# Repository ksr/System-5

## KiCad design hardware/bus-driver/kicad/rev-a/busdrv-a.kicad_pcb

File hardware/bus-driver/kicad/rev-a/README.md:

# System-5 Bus Driver Rev A (BUSDRV-A): KiCad master

> **AS ORDERED 2026-10-09 (JLCPCB 2000765A-Y53): SCRAP. Kept as the record of what was made; do not order from it.**
> This board file has four copper layers (inherited from memory Rev D's Eagle import), and Freerouting put 234 of its 247 track segments on In1/In2. The 2-layer zip held only the top and bottom copper, so the made boards have only GND (the pours), -INT, SDA, Q and one +5V segment; `tools/check_order_zip.py` fails this zip. Found 2026-10-19.
> **The replacement is Rev B (BUSDRV-B), `../rev-b/`:** the same circuit re-routed as a true 2-layer board, with 0.1" bypass caps.

A System-5 card modelled on the YACC1 bus tester. An **Arduino Nano** on USB drives two **MCP23017** I²C expanders wired straight onto the 30-pin System-5 bus.
- With the **CPU card removed**, it is bus master: it can read and write memory and I/O cards by running the 1802's bus cycle itself.
- With the **CPU in**, it only monitors.

Designed 2026-10-06. Generated by `gen/` from one netlist (`gen/netlist.py`). Edit `gen/netlist.py` and re-run the scripts, or edit in KiCad and drop the generator.

## Circuit

| Part | What it does |
|---|---|
| A1 Arduino Nano | USB serial console. I²C on A4 (SDA) and A5 (SCL). D2/D3 take the expanders' INTA. D4 drives XRST (both expanders' reset). A0 reads BUS_SENSE. |
| U1 MCP23017 @ 0x20 | GPA0–6 = D0–D6, GPB0–6 = A0–A6, GPA7/GPB7 = SPARE1/SPARE2 |
| U2 MCP23017 @ 0x21 | GPA0–6 = D7, A7, TPA, TPB, -MRD, -MRW, -VMA. GPB0–6 = Q, -RESET, -INT, -EF, N0, N1, N2. GPA7/GPB7 = SPARE3/SPARE4. |
| J1 | System-5 30-pin bus. Same footprint and position as on every System-5 card. |
| J2 | SPARE1–4 (outputs only), +5V, GND, for flying leads or later the CPU card's mode lines |
| R1, R2 4.7k | I²C pull-ups, to bus +5V |
| R3 10k | XRST pull-up, to bus +5V |
| R4 10k / R5 100k | Bus +5V sense into A0 (reads about 4.5 V when the bus is up) |
| R6 470 / D1 | Bus power LED |
| C1, C2 0.1 µF / C3 10 µF | Bypass and bulk |

**Design points:**
- **Output-only pins:** MCP23017 **GPA7/GPB7 are output-only** on current silicon (Microchip datasheet). So all 28 bus signals sit on bidirectional pins, which can be read when monitoring. The four output-only pins are the spares.
- **Power:**
  - The Nano runs from its USB port; its +5V pin is *not* connected to the bus.
  - The expanders and pull-ups run from bus +5V.
  - So USB never feeds a powered-down System-5.

  The firmware should keep D4 low and SDA/SCL released while BUS_SENSE shows the bus is off. Otherwise the Nano's pins back-feed the unpowered expanders through their protection diodes.
- **Bus lines:**
  - The bus lines are connected directly, without series resistors (Ken's choice, as on YACC1).
  - Open-collector lines (-RESET, -INT, -EF) must only ever be driven low or left floating (firmware).
  - The firmware must not drive the bus with the CPU card plugged in: the 1802 drives its address lines even in reset.
- **At power-up and on XRST:** the MCP23017 pins are inputs, so the card is quiet on the bus until the firmware decides otherwise.

## Board

- **Size and layout:** 140.95 × 96.19 mm, 2 layers. The System-5 card outline and bus connector position are taken from the Memory Rev D board.
  - The Nano sits on the right, with its USB socket at the card's outer edge.
  - The power LED is in the standard System-5 position.
- **Routing:** Freerouting; 247 track segments, 7 vias. Signals 0.25 mm, +5V/GND 0.6 mm, GND pour on both sides. JLCPCB 2-layer rules.
- **Checks, 2026-10-06:**
  - ERC: 0.
  - Netlist proof: MATCH, 41/41 nets.
  - DRC: 0 violations, 0 unconnected.
  - Schematic parity: 0.
- **Silkscreen:** chip labels with function and I²C address; "R1 4.7k"-style values; spare-header pin names; title `BUSDRV-A`.

**Check before ordering:** the Nano on female headers stands about 15–20 mm tall. Make sure that fits the card pitch in the System-5 cage, and that a USB cable can reach the card's outer edge with the card installed.

## Files

| File | What it is |
|---|---|
| `busdrv-a.kicad_pro/.kicad_sch/.kicad_pcb` | The project |
| `busdrv.pretty/C30.kicad_mod` | System-5 bus connector footprint (from the Eagle C30 package) |
| `busdrv-a-gerbers.zip` (and `gerbers/`) | **Upload to JLCPCB**: 2 layers, 1.6 mm |
| `busdrv-a-bom.csv` | Parts list (stock KiCad footprints; all through-hole) |
| `busdrv-a-schematic.pdf`, `-placement.pdf`, `-render-top.png`, `-render-bottom.png` | Prints and pictures |
| `reports/` | Netlist, DRC, ERC |
| `gen/netlist.py`, `make_schematic.py`, `make_board.py` | The generator: netlist → schematic → board |

To regenerate:

```bash
python3 gen/make_schematic.py
```
```bash
kicad-cli sch export netlist --format kicadsexpr -o reports/netlist.net busdrv-a.kicad_sch
```
```bash
<KiCad python> gen/make_board.py
```

Then route as in `tools/kicad/kicad_route.py`.

## Firmware and host tool

- **Firmware:** `embedded/bus-driver/s5-bus-driver`. It compiles for the Nano with arduino-cli. It never ran on a Rev A board (scrap); it has run on BUSDRV-B since 2026-10-30 (`../rev-b/README.md`).
- **Host tool:** `software/busdrv/s5busdrv.py`, with a simulator and tests.
- **Machine cycle:** both run the 1802 cycle: high address byte on A0–7 with a TPA pulse, low byte, -VMA low, then -MRD (read D0–D7) or data on D0–D7 with a -MRW pulse.

Open items for this card are in `BACKLOG.md`.

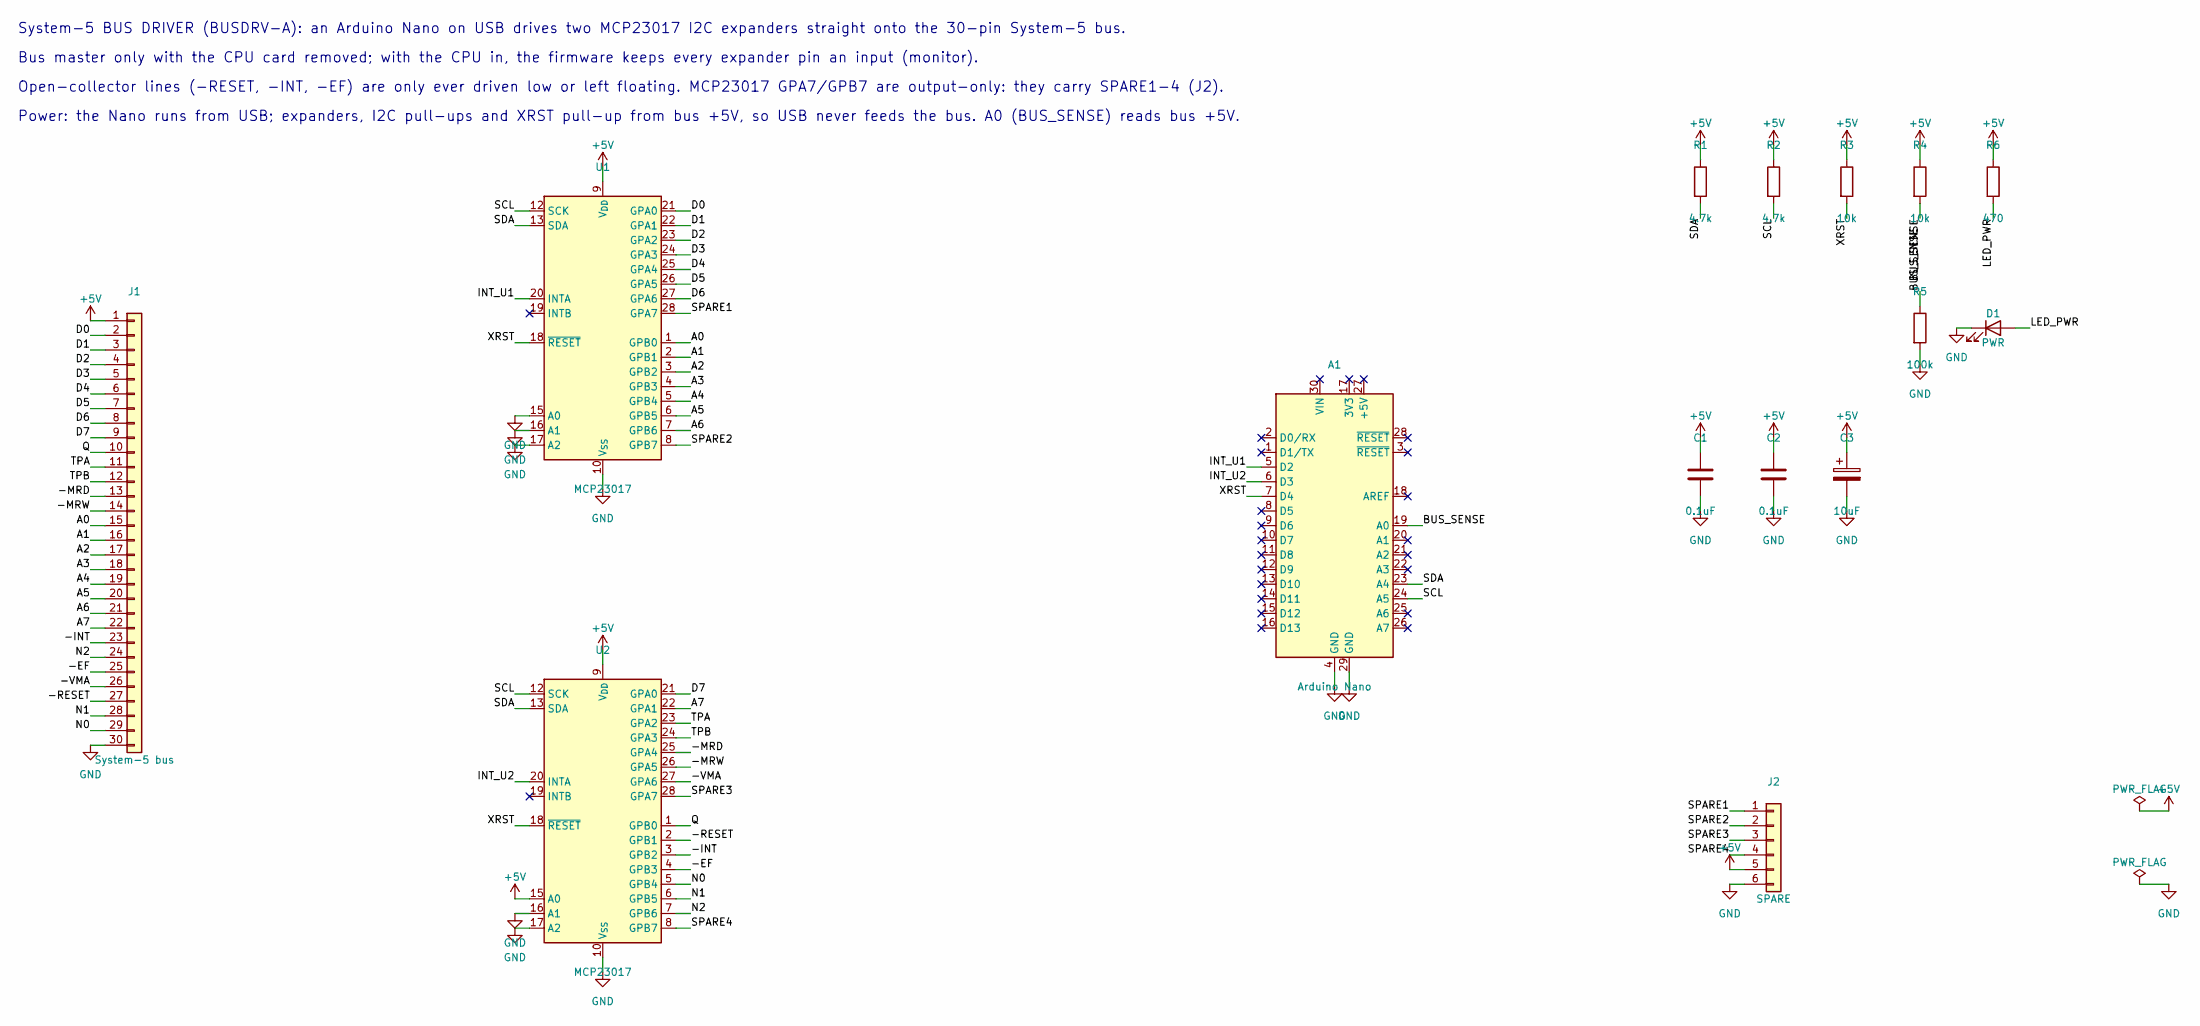
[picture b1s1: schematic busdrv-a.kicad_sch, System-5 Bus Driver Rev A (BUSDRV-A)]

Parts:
A1: Arduino Nano; Arduino_Nano
C1, C2: 0.1uF; C_Disc_D5.0mm_W2.5mm_P5.00mm
C3: 10uF; CP_Radial_D5.0mm_P2.00mm
D1: PWR; LED_D5.0mm
J1: System-5 bus; C30
J2: SPARE; PinHeader_1x06_P2.54mm_Vertical
R1, R2: 4.7k; R_Axial_DIN0207_L6.3mm_D2.5mm_P7.62mm_Horizontal
R3, R4: 10k; R_Axial_DIN0207_L6.3mm_D2.5mm_P7.62mm_Horizontal
R5: 100k; R_Axial_DIN0207_L6.3mm_D2.5mm_P7.62mm_Horizontal
R6: 470; R_Axial_DIN0207_L6.3mm_D2.5mm_P7.62mm_Horizontal
U1, U2: MCP23017; DIP-28_W7.62mm

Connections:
+5V: C1.1, C2.1, C3.1, J1.1, J2.5, R1.1, R2.1, R3.1, R4.1, R6.1, U1.9 (V_{DD}), U2.9 (V_{DD}), U2.15 (A0)
/-EF: J1.25, U2.4 (GPB3)
/-INT: J1.23, U2.3 (GPB2)
/-MRD: J1.13, U2.25 (GPA4)
/-MRW: J1.14, U2.26 (GPA5)
/-RESET: J1.27, U2.2 (GPB1)
/-VMA: J1.26, U2.27 (GPA6)
/A0: J1.15, U1.1 (GPB0)
/A1: J1.16, U1.2 (GPB1)
/A2: J1.17, U1.3 (GPB2)
/A3: J1.18, U1.4 (GPB3)
/A4: J1.19, U1.5 (GPB4)
/A5: J1.20, U1.6 (GPB5)
/A6: J1.21, U1.7 (GPB6)
/A7: J1.22, U2.22 (GPA1)
/BUS_SENSE: A1.19 (A0), R4.2, R5.1
/D0: J1.2, U1.21 (GPA0)
/D1: J1.3, U1.22 (GPA1)
/D2: J1.4, U1.23 (GPA2)
/D3: J1.5, U1.24 (GPA3)
/D4: J1.6, U1.25 (GPA4)
/D5: J1.7, U1.26 (GPA5)
/D6: J1.8, U1.27 (GPA6)
/D7: J1.9, U2.21 (GPA0)
/INT_U1: A1.5 (D2), U1.20 (INTA)
/INT_U2: A1.6 (D3), U2.20 (INTA)
/LED_PWR: D1.2 (A), R6.2
/N0: J1.29, U2.5 (GPB4)
/N1: J1.28, U2.6 (GPB5)
/N2: J1.24, U2.7 (GPB6)
/Q: J1.10, U2.1 (GPB0)
/SCL: A1.24 (A5), R2.2, U1.12 (SCK), U2.12 (SCK)
/SDA: A1.23 (A4), R1.2, U1.13 (SDA), U2.13 (SDA)
/SPARE1: J2.1, U1.28 (GPA7)
/SPARE2: J2.2, U1.8 (GPB7)
/SPARE3: J2.3, U2.28 (GPA7)
/SPARE4: J2.4, U2.8 (GPB7)
/TPA: J1.11, U2.23 (GPA2)
/TPB: J1.12, U2.24 (GPA3)
/XRST: A1.7 (D4), R3.2, U1.18 (~RESET), U2.18 (~RESET)
GND: A1.4 (GND), A1.29 (GND), C1.2, C2.2, C3.2, D1.1 (K), J1.30, J2.6, R5.2, U1.10 (V_{SS}), U1.15 (A0), U1.16 (A1), U1.17 (A2), U2.10 (V_{SS}), U2.16 (A1), U2.17 (A2)

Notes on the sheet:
System-5 BUS DRIVER (BUSDRV-A): an Arduino Nano on USB drives two MCP23017 I2C expanders straight onto the 30-pin System-5 bus.
Bus master only with the CPU card removed; with the CPU in, the firmware keeps every expander pin an input (monitor).
Open-collector lines (-RESET, -INT, -EF) are only ever driven low or left floating. MCP23017 GPA7/GPB7 are output-only: they carry SPARE1-4 (J2).
Power: the Nano runs from USB; expanders, I2C pull-ups and XRST pull-up from bus +5V, so USB never feeds the bus. A0 (BUS_SENSE) reads bus +5V.

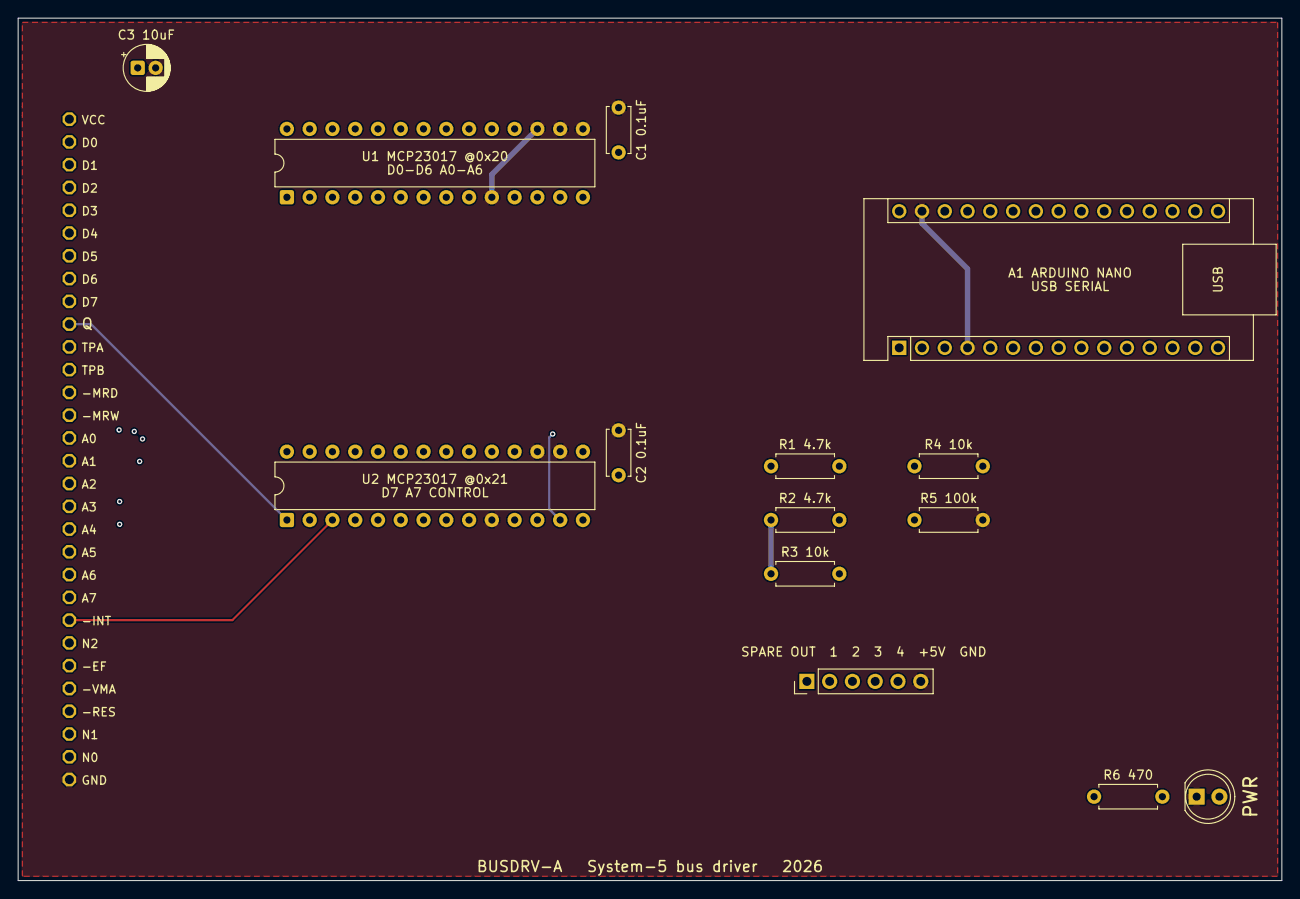
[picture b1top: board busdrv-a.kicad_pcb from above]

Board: 4 copper layers, 140.9 x 96.2 mm, 15 parts (0 on the bottom side), 41 nets.

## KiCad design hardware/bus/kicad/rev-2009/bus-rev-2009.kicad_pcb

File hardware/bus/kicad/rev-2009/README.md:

# bus-rev-2009 — KiCad conversion

Generated 2026-10-26 by `tools/eagle_to_kicad_all.py` from the Fusion XML export of the Eagle design `bus` in `hardware/bus/eagle/rev-2009/fusion-export/`. **The Eagle files are the record of what was designed and built; this KiCad project is derived from them and is regenerated from scratch on every run of the tool** (hand edits here will be lost - once a card is edited in KiCad, remove it from the tool's list). This revision was never fabricated (or its build status is unknown, see `hardware/FABRICATED.md`).

## Files

| File | What it is |
|---|---|
| `bus-rev-2009.kicad_pro` | project; DRC uses OSH Park rules (6 mil track, 5 mil clearance, 10 mil drill, 4 mil annular) as a modern-fab check, not the 2005 fab's rules |
| `bus-rev-2009.kicad_sch` | root sheet; 1 sub-sheet(s) `bus-rev-2009-sheetN.kicad_sch` mirror the Eagle sheets |
| `bus-rev-2009-eagle.kicad_sym` | project symbol library generated from the Eagle libraries used (units = Eagle gates) |
| `bus-rev-2009.kicad_pcb` | the board: 4 copper layers, 15 footprints, 200 track segments, 0 vias; 2 items on unmapped Eagle layers dropped |
| `bus-rev-2009-eagle.pretty/` | project footprint library extracted from the imported board |
| `reports/` | ERC (`erc.json`), DRC (`drc.json`), schematic PDF, board renders (`-top.png`, `-bottom.png`), netlist + `netlist-compare.txt` |

## Proof

Schematic-vs-board netlist comparison (`tools/kicad/compare_netlists.py`: every (reference, pad) partition must be identical): **MATCH (36/36 nets)**

```
  same connectivity, different net name: [('/Sheet 1/5V', '5V'), ('/Sheet 1/A0', 'A0'), ('/Sheet 1/A1', 'A1'), ('/Sheet 1/A2', 'A2'), ('/Sheet 1/A3', 'A3'), ('/Sheet 1/A4', 'A4'), ('/Sheet 1/A5', 'A5'), ('/Sheet 1/A6', 'A6'), ('/Sheet 1/A7', 'A7'), ('/Sheet 1/D0', 'D0'), ('/Sheet 1/D1', 'D1'), ('/Sheet 1/D2', 'D2'), ('/Sheet 1/D3', 'D3'), ('/Sheet 1/D4', 'D4'), ('/Sheet 1/D5', 'D5'), ('/Sheet 1/D6', 'D6'), ('/Sheet 1/D7', 'D7'), ('/Sheet 1/EF', 'EF'), ('/Sheet 1/EF1', 'EF1'), ('/Sheet 1/EF2', 'EF2'), ('/Sheet 1/EF3', 'EF3'), ('/Sheet 1/EXP', 'EXP'), ('/Sheet 1/INP', 'INP'), ('/Sheet 1/INT', 'INT'), ('/Sheet 1/MRD', 'MRD'), ('/Sheet 1/MRW', 'MRW'), ('/Sheet 1/N0', 'N0'), ('/Sheet 1/N1', 'N1'), ('/Sheet 1/N2', 'N2'), ('/Sheet 1/OUT', 'OUT'), ('/Sheet 1/Q', 'Q'), ('/Sheet 1/RESET', 'RESET'), ('/Sheet 1/TPA', 'TPA'), ('/Sheet 1/TPB', 'TPB'), ('/Sheet 1/VMA', 'VMA')]
```

## Readability

`tools/kicad/sch_overlaps.py` over every sheet: text over text 0, text over a symbol body 6, text crossed by a line 0, items off the drawing frame or on the title block 0. What is left is mostly the Eagle drawing itself (parts placed that close in Eagle) or KiCad drawing pin numbers centred on short pins.

## Residual ERC / DRC

ERC by type: power_pin_not_driven 2, unconnected_wire_endpoint 60.
`isolated_pin_label` = the converter's per-net global labels (cosmetic); `power_pin_not_driven` / unused-unit notes are the same ones KiCad's own Eagle importer leaves. `unconnected_wire_endpoint` / `pin_not_connected` = wire stubs Eagle leaves bare (mostly net wires ending on a bus, which is drawn as graphics here); since 2026-09-23 the converter no longer hangs a label on every such end (that was most of the label clutter), so they show as KiCad warnings.

DRC by type: shorting_items 1, silk_over_copper 7, solder_mask_bridge 1, track_dangling 3; unconnected items 0; schematic parity 0.
Silk-over-pad and clearance notes reflect the Eagle design as drawn; unconnected items are Eagle airwires (parts the design left unrouted).

Converter: converted: 8 symbols, 216 wires, 217 labels, 0 junctions, 6 bus lines, 2 no-connects

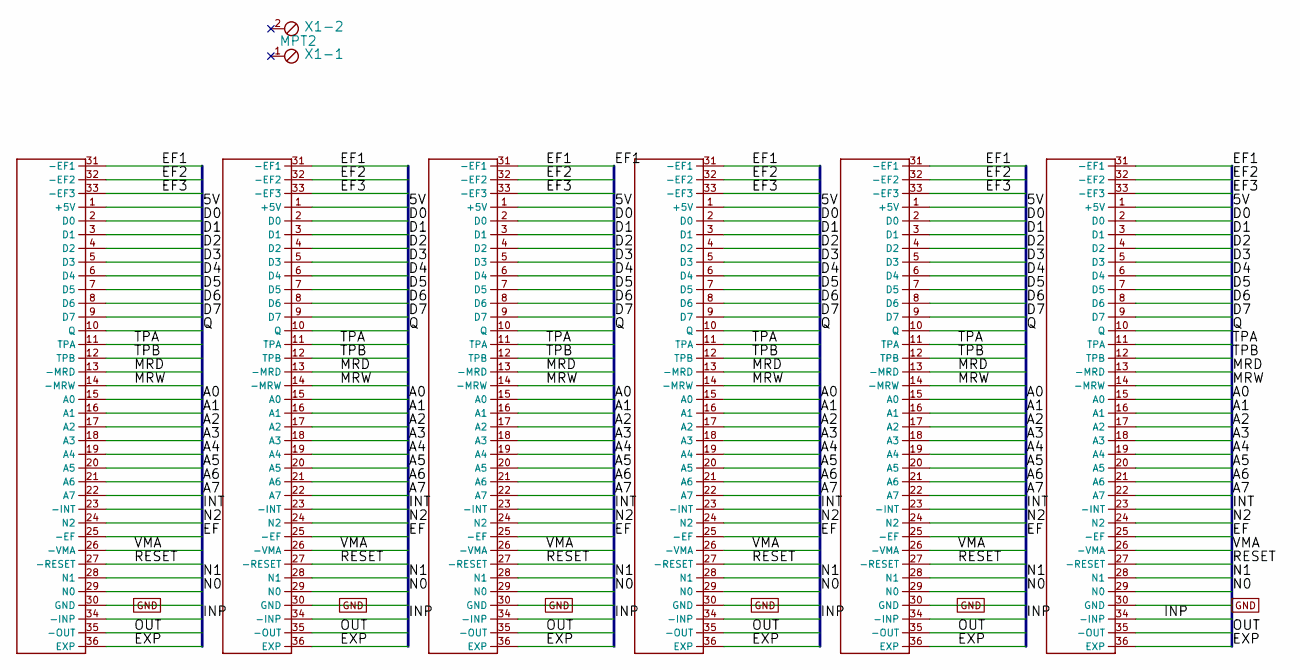
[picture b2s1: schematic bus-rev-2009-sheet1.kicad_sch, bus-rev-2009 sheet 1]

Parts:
U$1, U$2, U$3, U$4, U$5, U$6: C36A
X1: MPT2; 2POL254

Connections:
5V: U$1.1 (+5V), U$2.1 (+5V), U$3.1 (+5V), U$4.1 (+5V), U$5.1 (+5V), U$6.1 (+5V)
A0: U$1.15 (A0), U$2.15 (A0), U$3.15 (A0), U$4.15 (A0), U$5.15 (A0), U$6.15 (A0)
A1: U$1.16 (A1), U$2.16 (A1), U$3.16 (A1), U$4.16 (A1), U$5.16 (A1), U$6.16 (A1)
A2: U$1.17 (A2), U$2.17 (A2), U$3.17 (A2), U$4.17 (A2), U$5.17 (A2), U$6.17 (A2)
A3: U$1.18 (A3), U$2.18 (A3), U$3.18 (A3), U$4.18 (A3), U$5.18 (A3), U$6.18 (A3)
A4: U$1.19 (A4), U$2.19 (A4), U$3.19 (A4), U$4.19 (A4), U$5.19 (A4), U$6.19 (A4)
A5: U$1.20 (A5), U$2.20 (A5), U$3.20 (A5), U$4.20 (A5), U$5.20 (A5), U$6.20 (A5)
A6: U$1.21 (A6), U$2.21 (A6), U$3.21 (A6), U$4.21 (A6), U$5.21 (A6), U$6.21 (A6)
A7: U$1.22 (A7), U$2.22 (A7), U$3.22 (A7), U$4.22 (A7), U$5.22 (A7), U$6.22 (A7)
D0: U$1.2 (D0), U$2.2 (D0), U$3.2 (D0), U$4.2 (D0), U$5.2 (D0), U$6.2 (D0)
D1: U$1.3 (D1), U$2.3 (D1), U$3.3 (D1), U$4.3 (D1), U$5.3 (D1), U$6.3 (D1)
D2: U$1.4 (D2), U$2.4 (D2), U$3.4 (D2), U$4.4 (D2), U$5.4 (D2), U$6.4 (D2)
D3: U$1.5 (D3), U$2.5 (D3), U$3.5 (D3), U$4.5 (D3), U$5.5 (D3), U$6.5 (D3)
D4: U$1.6 (D4), U$2.6 (D4), U$3.6 (D4), U$4.6 (D4), U$5.6 (D4), U$6.6 (D4)
D5: U$1.7 (D5), U$2.7 (D5), U$3.7 (D5), U$4.7 (D5), U$5.7 (D5), U$6.7 (D5)
D6: U$1.8 (D6), U$2.8 (D6), U$3.8 (D6), U$4.8 (D6), U$5.8 (D6), U$6.8 (D6)
D7: U$1.9 (D7), U$2.9 (D7), U$3.9 (D7), U$4.9 (D7), U$5.9 (D7), U$6.9 (D7)
EF: U$1.25 (-EF), U$2.25 (-EF), U$3.25 (-EF), U$4.25 (-EF), U$5.25 (-EF), U$6.25 (-EF)
EF1: U$1.31 (-EF1), U$2.31 (-EF1), U$3.31 (-EF1), U$4.31 (-EF1), U$5.31 (-EF1), U$6.31 (-EF1)
EF2: U$1.32 (-EF2), U$2.32 (-EF2), U$3.32 (-EF2), U$4.32 (-EF2), U$5.32 (-EF2), U$6.32 (-EF2)
EF3: U$1.33 (-EF3), U$2.33 (-EF3), U$3.33 (-EF3), U$4.33 (-EF3), U$5.33 (-EF3), U$6.33 (-EF3)
EXP: U$1.36 (EXP), U$2.36 (EXP), U$3.36 (EXP), U$4.36 (EXP), U$5.36 (EXP), U$6.36 (EXP)
GND: U$1.30 (GND), U$2.30 (GND), U$3.30 (GND), U$4.30 (GND), U$5.30 (GND), U$6.30 (GND)
INP: U$1.34 (-INP), U$2.34 (-INP), U$3.34 (-INP), U$4.34 (-INP), U$5.34 (-INP), U$6.34 (-INP)
INT: U$1.23 (-INT), U$2.23 (-INT), U$3.23 (-INT), U$4.23 (-INT), U$5.23 (-INT), U$6.23 (-INT)
MRD: U$1.13 (-MRD), U$2.13 (-MRD), U$3.13 (-MRD), U$4.13 (-MRD), U$5.13 (-MRD), U$6.13 (-MRD)
MRW: U$1.14 (-MRW), U$2.14 (-MRW), U$3.14 (-MRW), U$4.14 (-MRW), U$5.14 (-MRW), U$6.14 (-MRW)
N0: U$1.29 (N0), U$2.29 (N0), U$3.29 (N0), U$4.29 (N0), U$5.29 (N0), U$6.29 (N0)
N1: U$1.28 (N1), U$2.28 (N1), U$3.28 (N1), U$4.28 (N1), U$5.28 (N1), U$6.28 (N1)
N2: U$1.24 (N2), U$2.24 (N2), U$3.24 (N2), U$4.24 (N2), U$5.24 (N2), U$6.24 (N2)
OUT: U$1.35 (-OUT), U$2.35 (-OUT), U$3.35 (-OUT), U$4.35 (-OUT), U$5.35 (-OUT), U$6.35 (-OUT)
Q: U$1.10 (Q), U$2.10 (Q), U$3.10 (Q), U$4.10 (Q), U$5.10 (Q), U$6.10 (Q)
RESET: U$1.27 (-RESET), U$2.27 (-RESET), U$3.27 (-RESET), U$4.27 (-RESET), U$5.27 (-RESET), U$6.27 (-RESET)
TPA: U$1.11 (TPA), U$2.11 (TPA), U$3.11 (TPA), U$4.11 (TPA), U$5.11 (TPA), U$6.11 (TPA)
TPB: U$1.12 (TPB), U$2.12 (TPB), U$3.12 (TPB), U$4.12 (TPB), U$5.12 (TPB), U$6.12 (TPB)
VMA: U$1.26 (-VMA), U$2.26 (-VMA), U$3.26 (-VMA), U$4.26 (-VMA), U$5.26 (-VMA), U$6.26 (-VMA)

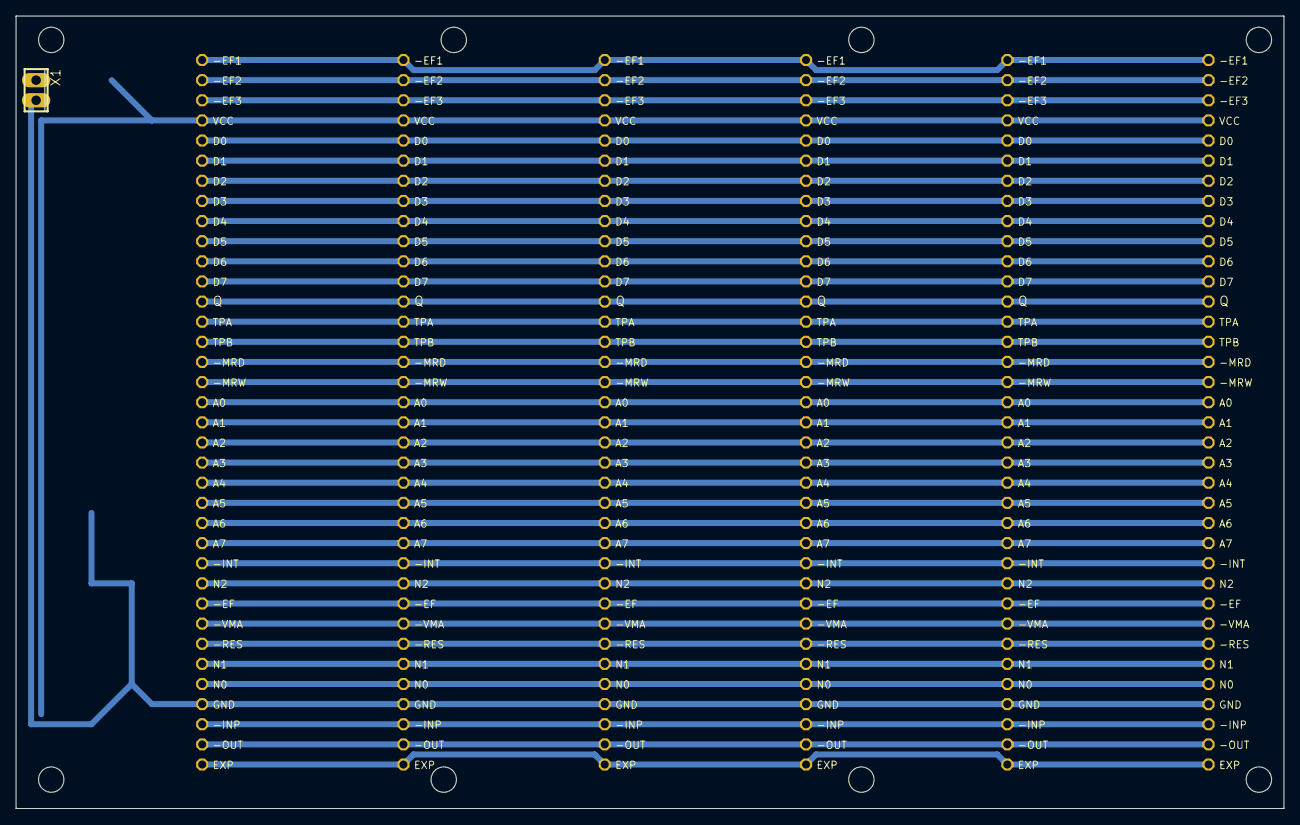
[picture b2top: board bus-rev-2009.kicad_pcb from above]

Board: 4 copper layers, 160.0 x 100.0 mm, 15 parts (0 on the bottom side), 36 nets.

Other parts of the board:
UNK_HOLE_0: dummyfp0
UNK_HOLE_1: dummyfp1
UNK_HOLE_2: dummyfp2
UNK_HOLE_3: dummyfp3
UNK_HOLE_4: dummyfp4
UNK_HOLE_5: dummyfp5
UNK_HOLE_6: dummyfp6
UNK_HOLE_7: dummyfp7

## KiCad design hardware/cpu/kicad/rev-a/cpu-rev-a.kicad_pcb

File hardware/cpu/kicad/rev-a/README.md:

# cpu-rev-a — KiCad conversion

Generated 2026-10-06 by `tools/eagle_to_kicad_all.py` from the Fusion XML export of the Eagle design `cpu2-a` in `hardware/cpu/eagle/rev-a/fusion-export/`. **The Eagle files are the record of what was designed and built; this KiCad project is derived from them and is regenerated from scratch on every run of the tool** (hand edits here will be lost - once a card is edited in KiCad, remove it from the tool's list). This revision was FABRICATED (see `hardware/FABRICATED.md`).

## Files

| File | What it is |
|---|---|
| `cpu-rev-a.kicad_pro` | project; DRC uses OSH Park rules (6 mil track, 5 mil clearance, 10 mil drill, 4 mil annular) as a modern-fab check, not the 2005 fab's rules |
| `cpu-rev-a.kicad_sch` | root sheet; 1 sub-sheet(s) `cpu-rev-a-sheetN.kicad_sch` mirror the Eagle sheets |
| `cpu-rev-a-eagle.kicad_sym` | project symbol library generated from the Eagle libraries used (units = Eagle gates) |
| `cpu-rev-a.kicad_pcb` | the board: 4 copper layers, 61 footprints, 1465 track segments, 291 vias; 2 items on unmapped Eagle layers dropped |
| `cpu-rev-a-eagle.pretty/` | project footprint library extracted from the imported board |
| `reports/` | ERC (`erc.json`), DRC (`drc.json`), schematic PDF, board renders (`-top.png`, `-bottom.png`), netlist + `netlist-compare.txt` |

## Proof

Schematic-vs-board netlist comparison (`tools/kicad/compare_netlists.py`: every (reference, pad) partition must be identical): **MATCH (88/88 nets)**

```
  same connectivity, different net name: [('/Sheet 1/-EF4', '-EF4'), ('/Sheet 1/-INT', '-INT'), ('/Sheet 1/-LOAD', '-LOAD'), ('/Sheet 1/-MRD', '-MRD'), ('/Sheet 1/-MRW', '-MRW'), ('/Sheet 1/-PAUSE', '-PAUSE'), ('/Sheet 1/-RESET', '-RESET'), ('/Sheet 1/-RUN', '-RUN'), ('/Sheet 1/-VMA', '-VMA'), ('/Sheet 1/ADDR0', 'ADDR0'), ('/Sheet 1/ADDR1', 'ADDR1'), ('/Sheet 1/ADDR2', 'ADDR2'), ('/Sheet 1/ADDR3', 'ADDR3'), ('/Sheet 1/ADDR4', 'ADDR4'), ('/Sheet 1/ADDR5', 'ADDR5'), ('/Sheet 1/ADDR6', 'ADDR6'), ('/Sheet 1/ADDR7', 'ADDR7'), ('/Sheet 1/ADDR8', 'ADDR8'), ('/Sheet 1/ADDR9', 'ADDR9'), ('/Sheet 1/ADDR10', 'ADDR10'), ('/Sheet 1/ADDR11', 'ADDR11'), ('/Sheet 1/ADDR12', 'ADDR12'), ('/Sheet 1/ADDR13', 'ADDR13'), ('/Sheet 1/ADDR14', 'ADDR14'), ('/Sheet 1/ADDR15', 'ADDR15'), ('/Sheet 1/CLEAR', 'CLEAR'), ('/Sheet 1/DATA0', 'DATA0'), ('/Sheet 1/DATA1', 'DATA1'), ('/Sheet 1/DATA2', 'DATA2'), ('/Sheet 1/DATA3', 'DATA3'), ('/Sheet 1/DATA4', 'DATA4'), ('/Sheet 1/DATA5', 'DATA5'), ('/Sheet 1/DATA6', 'DATA6'), ('/Sheet 1/DATA7', 'DATA7'), ('/Sheet 1/DMA_IN', 'DMA_IN'), ('/Sheet 1/DMA_OUT', 'DMA_OUT'), ('/Sheet 1/EF1', 'EF1'), ('/Sheet 1/EF2', 'EF2'), ('/Sheet 1/EF3', 'EF3'), ('/Sheet 1/EF4', 'EF4'), ('/Sheet 1/FEF', 'FEF'), ('/Sheet 1/KEF', 'KEF'), ('/Sheet 1/LCLK', 'LCLK'), ('/Sheet 1/Q', 'Q'), ('/Sheet 1/SC0', 'SC0'), ('/Sheet 1/SC1', 'SC1'), ('/Sheet 1/TPA', 'TPA'), ('/Sheet 1/TPB', 'TPB'), ('/Sheet 1/VEF', 'VEF'), ('/Sheet 1/WAIT', 'WAIT'), ('Net-(IC2-~{CE})', 'N$3'), ('Net-(IC3A-I3)', 'N$22'), ('Net-(IC4A-I3)', 'N$24'), ('Net-(IC5A-C)', 'N$19'), ('Net-(IC5A-R{slash}C)', 'N$17'), ('Net-(IC5A-~{Q})', 'N$15'), ('Net-(IC6D-O)', 'N$25'), ('Net-(IC6F-O)', 'N$7'), ('Net-(IC7A-I0)', 'N$16'), ('Net-(IC7A-O)', 'N$18'), ('Net-(IC7B-O)', 'N$23'), ('Net-(IC7C-I0)', 'N$21'), ('Net-(IC7D-I0)', 'N$37'), ('Net-(IC7D-I1)', 'N$4'), ('Net-(IC7D-O)', 'N$1'), ('Net-(IC8A-Q)', 'N$27'), ('Net-(IC8B-~{Q})', 'N$6'), ('Net-(IC9-G1)', 'N$38'), ('Net-(IC9-G2A)', 'N$20'), ('Net-(IC9-Y0)', 'N$29'), ('Net-(IC9-Y1)', 'N$30'), ('Net-(IC9-Y2)', 'N$31'), ('Net-(IC9-Y3)', 'N$32'), ('Net-(IC9-Y4)', 'N$33'), ('Net-(IC9-Y5)', 'N$34'), ('Net-(IC9-Y6)', 'N$35'), ('Net-(IC9-Y7)', 'N$36'), ('Net-(LED1-C)', 'N$5'), ('Net-(LED2-C)', 'N$10'), ('Net-(LED3-C)', 'N$9'), ('Net-(LED4-PadA)', 'N$8'), ('Net-(LED5-PadA)', 'N$13'), ('Net-(S1-S1)', 'N$2'), ('Net-(U$1-N0)', 'N0'), ('Net-(U$1-N1)', 'N1'), ('Net-(U$1-N2)', 'N2')]
```

## Readability

`tools/kicad/sch_overlaps.py` over every sheet: text over text 5, text over a symbol body 12, text crossed by a line 11, items off the drawing frame or on the title block 0. What is left is mostly the Eagle drawing itself (parts placed that close in Eagle) or KiCad drawing pin numbers centred on short pins.

## Residual ERC / DRC

ERC by type: endpoint_off_grid 26, missing_input_pin 1, missing_power_pin 1, missing_unit 1, unconnected_wire_endpoint 11.
`isolated_pin_label` = the converter's per-net global labels (cosmetic); `power_pin_not_driven` / unused-unit notes are the same ones KiCad's own Eagle importer leaves. `unconnected_wire_endpoint` / `pin_not_connected` = wire stubs Eagle leaves bare (mostly net wires ending on a bus, which is drawn as graphics here); since 2026-09-23 the converter no longer hangs a label on every such end (that was most of the label clutter), so they show as KiCad warnings.

DRC by type: lib_footprint_mismatch 1, silk_edge_clearance 1, silk_over_copper 199, silk_overlap 28; unconnected items 0; schematic parity 0.
Silk-over-pad and clearance notes reflect the Eagle design as drawn; unconnected items are Eagle airwires (parts the design left unrouted).

Converter: converted: 88 symbols, 478 wires, 136 labels, 119 junctions, 12 bus lines, 12 no-connects

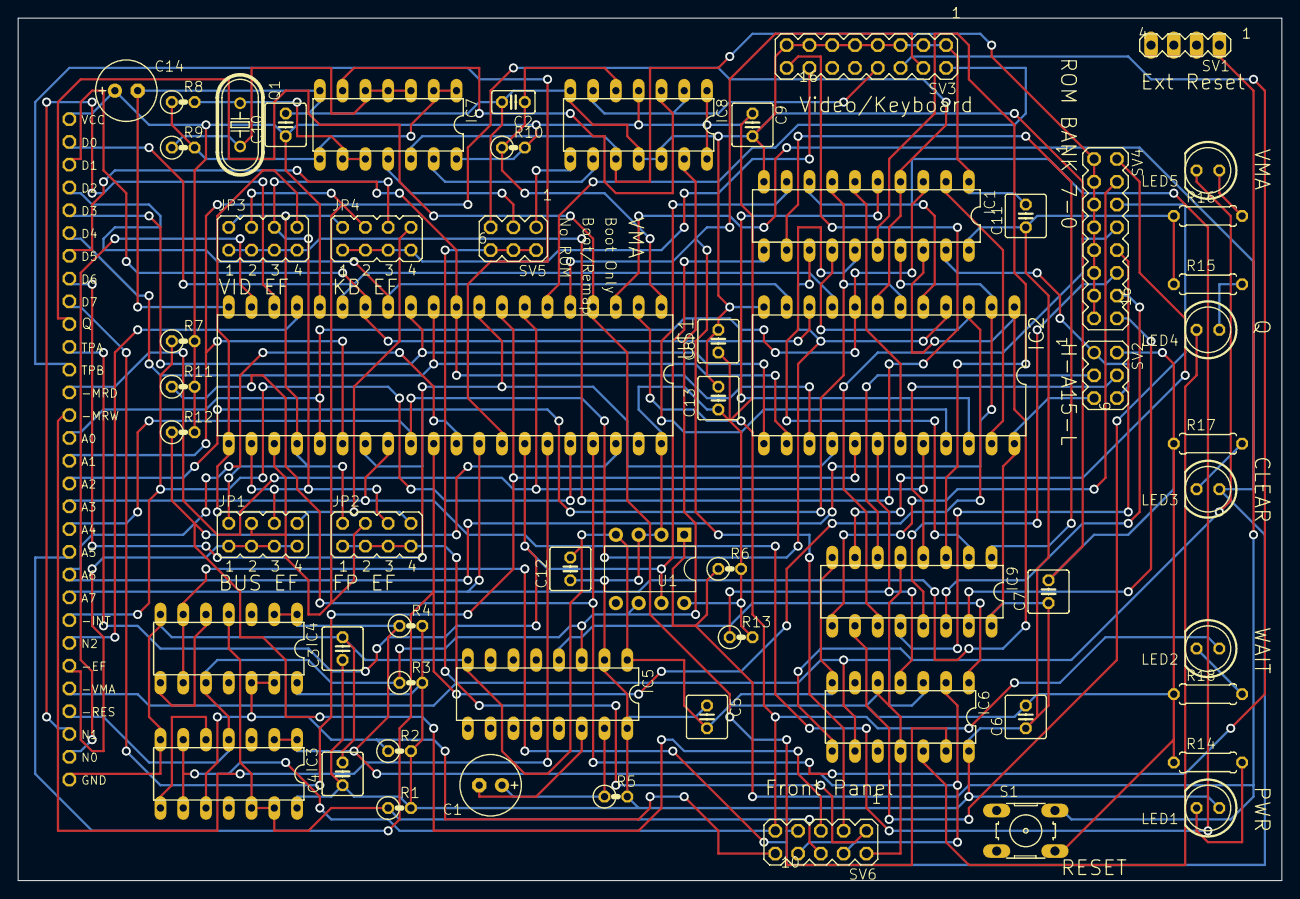
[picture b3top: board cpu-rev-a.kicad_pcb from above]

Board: 4 copper layers, 140.9 x 96.2 mm, 61 parts (0 on the bottom side), 88 nets.

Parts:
C1, C14: E2,5-7
C2: C025-025X050
C3, C4, C5, C6, C7, C8, C9, C10, C11, C12, C13: C025-050X050
IC1: 74LS373N; DIL20
IC2: BOOTROM; DIL24
IC3, IC4: 74LS20N; DIL14
IC5: 74LS123N; DIL16
IC6: 74LS05N; DIL14
IC7: 74LS00N; DIL14
IC8: 74LS74N; DIL14
IC9: 74S138N; DIL16
JP1, JP2, JP3, JP4: JP4Q
LED1, LED2, LED3, LED4, LED5: LED5MM
Q1: HC49U70
R1, R2, R3, R4, R5, R6, R7, R8, R9, R10, R11, R12, R13: 0207_2V
R14, R15, R16, R17, R18: 0207_7
S1: B3F-10XX
SV1: MA04-1
SV2, SV5: MA03-2
SV3, SV4: MA08-2
SV6: MA05-2
U1: CM1232; DIP-8
U$1: CDP1802BCECDP1802BCE; DIL40
U$2: C30

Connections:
-EF4: JP1.1, JP1.3, JP1.5, JP1.7, U$2.25
-INT: R7.1, U$1.36, U$2.23
-LOAD: IC3.10, IC4.12, IC4.13, R2.1, SV6.10
-MRD: IC2.20, U$1.7, U$2.13
-MRW: U$1.35, U$2.14
-PAUSE: IC3.12, IC3.13, IC4.4, R1.1, SV6.6
-RESET: IC3.4, IC4.10, IC5.3, IC8.13, R3.1, U1.6, U$2.27
-RUN: IC3.1, IC3.2, IC4.1, IC4.2, IC6.2, R4.1, SV6.4, SV6.8
-VMA: IC6.3, IC6.9, SV5.2, SV5.4, SV5.6, U$2.26
ADDR0: IC1.3, IC2.8, U$1.25, U$2.15
ADDR1: IC1.4, IC2.7, U$1.26, U$2.16
ADDR2: IC1.7, IC2.6, U$1.27, U$2.17
ADDR3: IC1.8, IC2.5, U$1.28, U$2.18
ADDR4: IC1.13, IC2.4, U$1.29, U$2.19
ADDR5: IC1.14, IC2.3, U$1.30, U$2.20
ADDR6: IC1.17, IC2.2, U$1.31, U$2.21
ADDR7: IC1.18, IC2.1, U$1.32, U$2.22
ADDR8: IC1.2, IC2.23
ADDR9: IC1.5, IC2.22
ADDR10: IC1.6, IC2.19
ADDR11: IC1.9, IC2.21
ADDR12: IC1.12, IC9.1
ADDR13: IC1.15, IC9.2
ADDR14: IC1.16, IC9.3
ADDR15: IC1.19, SV2.1, SV2.6
CLEAR: IC4.6, IC4.9, LED3.A, SV6.7, U$1.3
DATA0: IC2.9, U$1.15, U$2.2
DATA1: IC2.10, U$1.14, U$2.3
DATA2: IC2.11, U$1.13, U$2.4
DATA3: IC2.13, U$1.12, U$2.5
DATA4: IC2.14, U$1.11, U$2.6
DATA5: IC2.15, U$1.10, U$2.7
DATA6: IC2.16, U$1.9, U$2.8
DATA7: IC2.17, U$1.8, U$2.9
DMA_IN: R12.1, SV6.5, U$1.38
DMA_OUT: R11.1, SV3.6, U$1.37
EF1: JP1.2, JP2.2, JP3.2, JP4.2, U$1.24
EF2: JP1.4, JP2.4, JP3.4, JP4.4, U$1.23
EF3: JP1.6, JP2.6, JP3.6, JP4.6, U$1.22
EF4: JP1.8, JP2.8, JP3.8, JP4.8, U$1.21
FEF: JP2.1, JP2.3, JP2.5, JP2.7, SV6.1
GND: C2.2, C3.2, C4.2, C5.2, C6.2, C7.2, C8.2, C9.2, C10.2, C11.2, C12.2, C13.2, C14.-, IC1.1, IC1.10, IC2.12, IC3.7, IC4.7, IC5.1, IC5.8, IC6.5, IC6.7, IC6.11, IC7.7, IC8.7, IC8.11, IC8.12, IC9.5, IC9.8, R14.1, R17.1, R18.1, S1.4, SV2.2, SV3.1, SV3.3, SV3.5, SV3.7, SV3.9, SV3.11, SV3.13, SV3.15, SV5.5, SV6.2, U1.4, U$1.20, U$2.30
KEF: JP4.1, JP4.3, JP4.5, JP4.7, SV3.14
LCLK: IC8.2, IC8.6, SV3.8
N0: U$1.19, U$2.29
N1: U$1.18, U$2.28
N2: U$1.17, U$2.24
unnamed: IC7.11, SV5.3
unnamed: R6.1, S1.2, SV1.1, U1.1
unnamed: IC2.18, IC6.4, R13.1
unnamed: IC7.13, IC8.9
unnamed: LED1.K, R14.2
unnamed: IC8.8, SV5.1
unnamed: IC6.12, LED4.K
unnamed: LED4.A, R15.2
unnamed: LED3.K, R17.2
unnamed: LED2.K, R18.2
unnamed: LED5.A, R16.2
unnamed: IC5.4, IC6.1
unnamed: IC7.1, IC7.2, IC7.8, R8.1, R9.2
unnamed: C1.+, IC5.15, R5.1
unnamed: IC7.3, IC7.4, IC7.5, Q1.2, R9.1
unnamed: C1.-, IC5.14
unnamed: IC9.4, SV2.4
unnamed: IC7.9, IC7.10, Q1.1, R8.2
unnamed: IC3.5, IC3.8
unnamed: IC7.6, IC8.3
unnamed: IC4.5, IC4.8
unnamed: IC6.8, LED5.K
unnamed: C2.1, IC8.5, R10.1, U$1.1
unnamed: IC9.15, SV4.16
unnamed: IC9.14, SV4.14
unnamed: IC9.13, SV4.12
unnamed: IC9.12, SV4.10
unnamed: IC9.11, SV4.8
unnamed: IC9.10, SV4.6
unnamed: IC9.9, SV4.4
unnamed: IC9.7, SV4.2
unnamed: IC7.12, IC8.10, SV4.1, SV4.3, SV4.5, SV4.7, SV4.9, SV4.11, SV4.13, SV4.15
unnamed: IC9.6, SV2.3
Q: IC6.13, U$1.4, U$2.10
SC0: SV3.2, U$1.6
SC1: SV3.4, SV6.3, U$1.5
TPA: IC1.11, U1.7, U$1.34, U$2.11
TPB: U$1.33, U$2.12
VCC: C3.1, C4.1, C5.1, C6.1, C7.1, C8.1, C9.1, C10.1, C11.1, C12.1, C13.1, C14.+, IC1.20, IC2.24, IC3.14, IC4.14, IC5.2, IC5.16, IC6.14, IC7.14, IC8.1, IC8.4, IC8.14, IC9.16, LED1.A, R1.2, R2.2, R3.2, R4.2, R5.2, R6.2, R7.2, R10.2, R11.2, R12.2, R13.2, R15.1, R16.1, SV2.5, U1.2, U1.3, U1.8, U$1.16, U$1.40, U$2.1
VEF: JP3.1, JP3.3, JP3.5, JP3.7, SV3.16
WAIT: IC3.6, IC3.9, LED2.A, SV6.9, U$1.2

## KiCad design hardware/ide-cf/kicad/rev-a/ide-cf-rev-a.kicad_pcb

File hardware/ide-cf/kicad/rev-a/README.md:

# ide-cf-rev-a — KiCad conversion

Generated 2026-10-06 by `tools/eagle_to_kicad_all.py` from the Fusion XML export of the Eagle design `ide1-a` in `hardware/ide-cf/eagle/rev-a/fusion-export/`. **The Eagle files are the record of what was designed and built; this KiCad project is derived from them and is regenerated from scratch on every run of the tool** (hand edits here will be lost - once a card is edited in KiCad, remove it from the tool's list). This revision was FABRICATED (see `hardware/FABRICATED.md`).

## Files

| File | What it is |
|---|---|
| `ide-cf-rev-a.kicad_pro` | project; DRC uses OSH Park rules (6 mil track, 5 mil clearance, 10 mil drill, 4 mil annular) as a modern-fab check, not the 2005 fab's rules |
| `ide-cf-rev-a.kicad_sch` | root sheet; 1 sub-sheet(s) `ide-cf-rev-a-sheetN.kicad_sch` mirror the Eagle sheets |
| `ide-cf-rev-a-eagle.kicad_sym` | project symbol library generated from the Eagle libraries used (units = Eagle gates) |
| `ide-cf-rev-a.kicad_pcb` | the board: 4 copper layers, 24 footprints, 717 track segments, 115 vias; 2 items on unmapped Eagle layers dropped |
| `ide-cf-rev-a-eagle.pretty/` | project footprint library extracted from the imported board |
| `reports/` | ERC (`erc.json`), DRC (`drc.json`), schematic PDF, board renders (`-top.png`, `-bottom.png`), netlist + `netlist-compare.txt` |

## Proof

Schematic-vs-board netlist comparison (`tools/kicad/compare_netlists.py`: every (reference, pad) partition must be identical): **MATCH (49/49 nets)**

```
  same connectivity, different net name: [('/Sheet 1/D0', 'D0'), ('/Sheet 1/D1', 'D1'), ('/Sheet 1/D2', 'D2'), ('/Sheet 1/D3', 'D3'), ('/Sheet 1/D4', 'D4'), ('/Sheet 1/D5', 'D5'), ('/Sheet 1/D6', 'D6'), ('/Sheet 1/D7', 'D7'), ('/Sheet 1/IDERW', 'IDERW'), ('/Sheet 1/IDESEL', 'IDESEL'), ('/Sheet 1/INP', 'INP'), ('/Sheet 1/MRD', 'MRD'), ('/Sheet 1/N0', 'N0'), ('/Sheet 1/N1', 'N1'), ('/Sheet 1/N2', 'N2'), ('/Sheet 1/OUT', 'OUT'), ('/Sheet 1/PORT1', 'PORT1'), ('/Sheet 1/PORT2', 'PORT2'), ('/Sheet 1/PORT3', 'PORT3'), ('/Sheet 1/PORT4', 'PORT4'), ('/Sheet 1/PORT5', 'PORT5'), ('/Sheet 1/PORT6', 'PORT6'), ('/Sheet 1/PORT7', 'PORT7'), ('/Sheet 1/TPA', 'TPA'), ('/Sheet 1/TPB', 'TPB'), ('Net-(IC1A-I)', 'N$6'), ('Net-(IC1A-O)', 'N$7'), ('Net-(IC1B-I)', 'N$15'), ('Net-(IC1B-O)', 'N$23'), ('Net-(IC1C-O)', 'N$10'), ('Net-(IC1D-O)', 'N$12'), ('Net-(IC1E-I)', 'N$17'), ('Net-(IC1E-O)', 'N$13'), ('Net-(IC2A-I1)', 'N$11'), ('Net-(IC2A-O)', 'N$8'), ('Net-(IC2C-O)', 'N$14'), ('Net-(IC2D-O)', 'N$16'), ('Net-(IC5A-O)', 'N$9'), ('Net-(IC6B-O)', 'N$29'), ('Net-(IC6C-O)', 'N$30'), ('Net-(IC7-Q1)', 'N$24'), ('Net-(IC7-Q2)', 'N$25'), ('Net-(IC7-Q3)', 'N$26'), ('Net-(IC7-Q4)', 'N$27'), ('Net-(IC7-~{Q4})', 'N$28'), ('Net-(LED1-C)', 'N$22'), ('Net-(U$1--RESET)', 'RESET')]
```

## Readability

`tools/kicad/sch_overlaps.py` over every sheet: text over text 0, text over a symbol body 42, text crossed by a line 16, items off the drawing frame or on the title block 0. What is left is mostly the Eagle drawing itself (parts placed that close in Eagle) or KiCad drawing pin numbers centred on short pins.

## Residual ERC / DRC

ERC by type: endpoint_off_grid 24, unconnected_wire_endpoint 2.
`isolated_pin_label` = the converter's per-net global labels (cosmetic); `power_pin_not_driven` / unused-unit notes are the same ones KiCad's own Eagle importer leaves. `unconnected_wire_endpoint` / `pin_not_connected` = wire stubs Eagle leaves bare (mostly net wires ending on a bus, which is drawn as graphics here); since 2026-09-23 the converter no longer hangs a label on every such end (that was most of the label clutter), so they show as KiCad warnings.

DRC by type: silk_over_copper 116, silk_overlap 10; unconnected items 0; schematic parity 0.
Silk-over-pad and clearance notes reflect the Eagle design as drawn; unconnected items are Eagle airwires (parts the design left unrouted).

Converter: converted: 45 symbols, 318 wires, 35 labels, 69 junctions, 0 bus lines, 40 no-connects

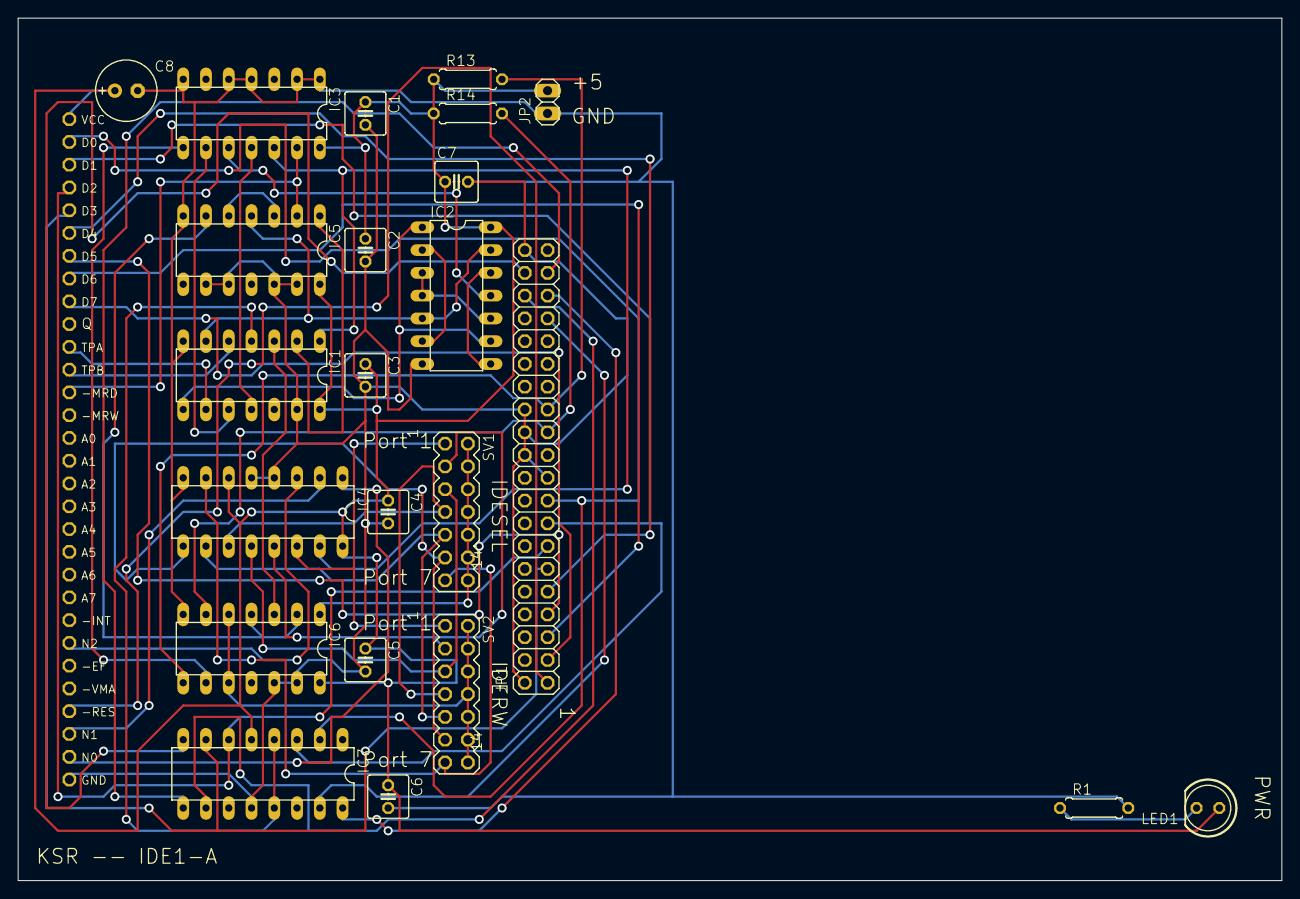
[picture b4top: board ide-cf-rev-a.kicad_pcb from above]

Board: 4 copper layers, 140.9 x 96.2 mm, 24 parts (0 on the bottom side), 49 nets.

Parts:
C1, C2, C3, C4, C5, C6, C7: .1; C025-050X050
C8: 10.0; E2,5-7
IC1: 74LS04N; DIL14
IC2, IC3: 74LS00N; DIL14
IC4: 74LS138N; DIL16
IC5: 74S32N; DIL14
IC6: 74LS32N; DIL14
IC7: 74LS75N; DIL16
JP1: 2X20
JP2: 1X02
LED1: LED5MM
R1: 470; 0207_7
R13, R14: 330; 0207_7
SV1, SV2: MA07-2
U$1: C30

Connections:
D0: IC7.2, JP1.17, U$1.2
D1: IC7.3, JP1.15, U$1.3
D2: IC7.6, JP1.13, U$1.4
D3: IC7.7, JP1.11, U$1.5
D4: JP1.9, U$1.6
D5: JP1.7, U$1.7
D6: JP1.5, U$1.8
D7: JP1.3, U$1.9
GND: C1.2, C2.2, C3.2, C4.2, C5.2, C6.2, C7.2, C8.-, IC1.7, IC1.13, IC2.7, IC3.1, IC3.2, IC3.4, IC3.5, IC3.7, IC4.4, IC4.5, IC4.8, IC5.7, IC5.9, IC5.10, IC5.12, IC5.13, IC6.7, IC6.12, IC6.13, IC7.12, JP1.2, JP1.19, JP1.22, JP1.24, JP1.26, JP1.40, JP2.1, R1.2, U$1.30
IDERW: IC6.5, IC6.10, SV2.2, SV2.4, SV2.6, SV2.8, SV2.10, SV2.12, SV2.14
IDESEL: IC6.1, SV1.2, SV1.4, SV1.6, SV1.8, SV1.10, SV1.12, SV1.14
INP: IC3.8, IC6.9
MRD: IC3.13, IC5.2, U$1.13
N0: IC4.1, U$1.29
N1: IC4.2, U$1.28
N2: IC4.3, U$1.24
unnamed: IC1.1, IC3.12, IC4.15
unnamed: IC1.2, IC5.1
unnamed: IC2.3, IC2.4, IC2.10
unnamed: IC5.3, IC5.5
unnamed: IC1.6, IC2.5, IC2.13, IC5.4
unnamed: IC2.2, IC2.6
unnamed: IC1.8, IC2.1, IC2.9
unnamed: IC1.10, IC3.9
unnamed: IC2.8, IC2.12
unnamed: IC1.3, IC6.3
unnamed: IC2.11, IC3.10
unnamed: IC1.11, IC3.11
unnamed: LED1.K, R1.1
unnamed: IC1.4, IC7.4, IC7.13
unnamed: IC7.16, JP1.35
unnamed: IC7.15, JP1.33
unnamed: IC7.10, JP1.36
unnamed: IC7.9, JP1.37
unnamed: IC7.8, JP1.38
unnamed: IC6.6, JP1.23, R14.2
unnamed: IC6.8, JP1.25, R13.2
OUT: IC5.6, IC6.2, IC6.4
PORT1: IC4.14, SV1.1, SV2.1
PORT2: IC4.13, SV1.3, SV2.3
PORT3: IC4.12, SV1.5, SV2.5
PORT4: IC4.11, SV1.7, SV2.7
PORT5: IC4.10, SV1.9, SV2.9
PORT6: IC4.9, SV1.11, SV2.11
PORT7: IC4.7, SV1.13, SV2.13
RESET: JP1.1, U$1.27
TPA: IC1.9, U$1.11
TPB: IC1.5, U$1.12
VCC: C1.1, C2.1, C3.1, C4.1, C5.1, C6.1, C7.1, C8.+, IC1.14, IC2.14, IC3.14, IC4.6, IC4.16, IC5.14, IC6.14, IC7.5, JP2.2, LED1.A, R13.1, R14.1, U$1.1
